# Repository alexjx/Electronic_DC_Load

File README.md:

# Electronic Controlled DC Dummy Load

An Arduino-compatible electronic load built around an ATmega328P. It draws a
controlled current from a DC source and displays the measured current, voltage,
power, temperature, and accumulated capacity.

> [!WARNING]
> This is an experimental high-power project, not a certified test instrument.
> The 15 A and 200 W values are firmware ceilings, not proven continuous hardware
> ratings. Safe operation depends on the input voltage, IRFP250N safe operating
> area, heatsink, airflow, shunt and PCB heating, wiring, connectors, calibration,
> and an external fuse. Begin with a current-limited supply at low power and do not
> leave the load unattended. The refactored firmware has not yet been validated on
> the physical hardware.

## Hardware overview

The load uses a power MOSFET as a variable resistance. A precision shunt measures
the resulting current, while the firmware adjusts a DAC until measured current
matches the requested value.

```text
Source under test -> J1 -> IRFP250N -> 5 mOhm shunt -> ground
                         ^                   |
                         |                   +-> INA213 -> AD7190 ADC
ATmega328P -> AD5541 DAC -> AD8629 gate-control amplifier
```

| Part | Purpose |
| --- | --- |
| ATmega328P-AU, 16 MHz | Runs the user interface, safety checks, and current controller |
| AD7190 | Measures load voltage and shunt current |
| AD5541 | Produces the analog current command |
| AD8629 | Buffers voltage sensing and drives the MOSFET control loop |
| INA213 and 5 mOhm / 4 W shunt | Measures load current |
| IRFP250N | Dissipates the power drawn from the source |
| LM35 | Measures heatsink temperature |
| 16x2 LCD and PCF8574 | Displays settings and measurements over I2C |
| REF5050 | Provides the 5 V ADC, DAC, and analog reference |

### Connections

| Connector | Function | Notes |
| --- | --- | --- |
| J1 | DC source under test | Schematic pad 2 is load positive; pad 1 is return/ground. Confirm this against the assembled PCB before applying power. |
| J2 | Control-power input | Feeds the MP1584 supply stage. The repository does not document a safe input-voltage range or jack polarity; verify the assembled board before use. |
| J3 | AVR ISP | Programming connector for the ATmega328P |
| J4 | Cooling fan | Nominal 12 V fan output controlled by the firmware |

The complete Eagle design is in [`schematic/`](schematic/). The design files
label the input-divider resistor as 9.9 kOhm, while the purchase record says the
fitted part is 9.09 kOhm. The firmware follows the purchase record; confirm the
assembled value and verify readings against calibrated meters before power testing.

## Controls and display

The top LCD row shows the current setpoint, cutoff voltage, and operating status.
A blank status means idle; `*` means the load is running. The LCD cursor identifies
the digit changed by the rotary encoder.

| Control | Action |
| --- | --- |
| Rotate encoder | Change the selected current or cutoff-voltage digit |
| S1 / D4 | Move the selected digit left |
| S4 / D6 | Move the selected digit right |
| S3 / D3 | Show the previous measurement page |
| S2 / D5 | Show the next measurement page |
| Hold encoder switch | Start loading after the controller has been idle for at least 3 seconds |
| Click encoder while running | Stop loading immediately |
| Click encoder on a cleared fault | Acknowledge the fault and return to idle |

The four bottom-row pages show:

1. Measured current and voltage.
2. Calculated power and heatsink temperature.
3. Session capacity in mAh.
4. Session energy in Wh.

The mAh and Wh counters reset whenever a new load session starts. The setpoints are
saved when a session starts or stops.

## Usage guide

1. With all power disconnected, inspect the board, fit an adequate heatsink and
   fan, and add a suitable external fuse to the source-under-test connection.
2. Confirm J1 polarity and the required J2 voltage and polarity from the actual
   assembled board. Connect the fan to J4, then apply control power to J2.
3. Check that the display starts normally and that no fault is reported. Verify the
   voltage, current, and temperature readings before enabling the power stage.
4. Use S1/S4 to select a digit and rotate the encoder to set the desired current and
   low-voltage cutoff. Start with a small current.
5. Turn the current-limited source off, connect it to J1 with the verified polarity,
   and then turn the source on.
6. After the controller has been idle for at least 3 seconds, hold the encoder switch
   until loading starts. Confirm that `*` appears and watch current, power, and
   temperature while testing.
7. Click the encoder to stop. Confirm that `*` disappears before disconnecting the
   source.

The firmware limits the setpoint to 15.000 A, reduces the current request above a
calculated 200 W, trips overcurrent at 16.5 A, and trips overtemperature at 95 degC.
These protections supplement rather than replace correctly rated hardware and an
external fuse.

### Faults

Any firmware fault commands the DAC to zero and latches the load off.

| Display | Meaning | Before acknowledging |
| --- | --- | --- |
| `FAULT ADC` | ADC did not initialize or respond in time | Check ADC power, SPI wiring, and ready signal |
| `FAULT TEMP SNS` | Temperature reading is outside the plausible sensor range | Check the LM35 and its wiring |
| `FAULT OVERCUR` | Measured current exceeded 16.5 A | Remove the cause of excess current |
| `FAULT UNDERVOLT` | Source voltage fell below the configured cutoff | Recharge, replace, or disconnect the source |
| `FAULT OVERTEMP` | Temperature exceeded 95 degC | Keep cooling active and wait for the load to cool |

After correcting the cause, click the encoder when the display says
`Click to ack`. Acknowledgement only returns the controller to idle; it does not
restart the load. A condition that is still unsafe will fault again or refuse to
clear.

## Firmware build and tests

Initialize the pinned libraries, then build the Arduino Uno firmware:

```sh
git submodule update --init --recursive
make -C code clean
make -C code
```

Run the hardware-independent safety and driver tests with:

```sh
make -C code/tests clean
make -C code/tests
```

See [`code/BUILDING.md`](code/BUILDING.md) for the tested Ubuntu/WSL environment,
tool versions, generated files, and current flashing limitations.

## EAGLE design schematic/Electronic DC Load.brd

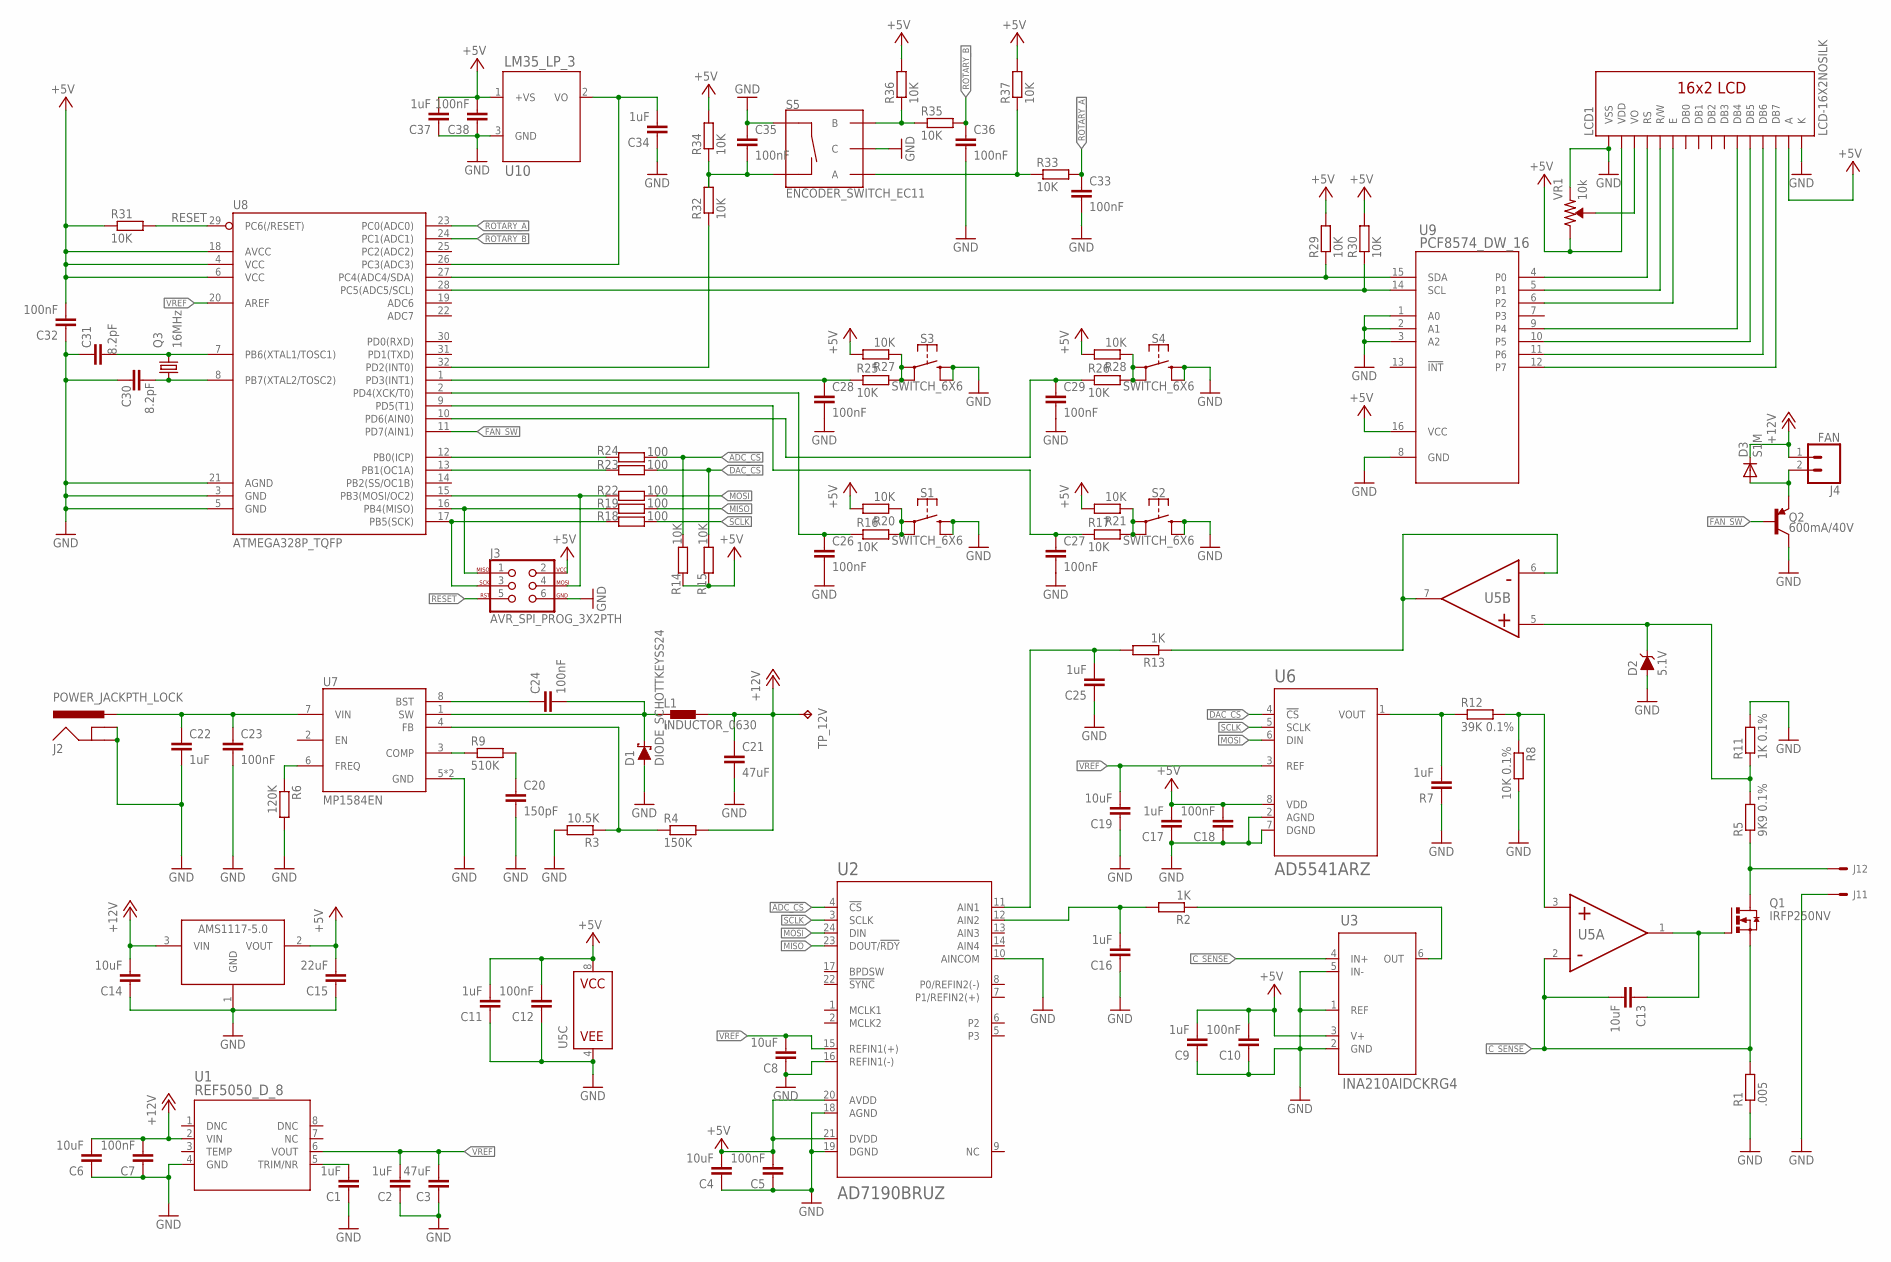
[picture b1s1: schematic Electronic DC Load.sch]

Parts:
C1, C2, C9, C11, C16, C17, C22, C25, C34, C37: 1uF; C0805
C3, C21: 47uF; C1206
C4, C6, C8, C13, C14, C19: 10uF; C1206
C5, C7, C10, C12, C18, C23, C24, C38: 100nF; C0805
C15: 22uF; C1206
C20: 150pF; C0402
C26, C27, C28, C29, C32, C33, C35, C36: 100nF; C0603
C30, C31: 8.2pF; C0603
D1: DIODE_SCHOTTKEYSS24; SMA-DIODE
D2: 5.1V; LL-34
D3: S1M; SMA
J1: KF762-2
J2: POWER_JACKPTH_LOCK; POWER_JACK_PTH_LOCK
J3: AVR_SPI_PROG_3X2PTH; 2X3
J4: FAN; 1X02_LOCK_LONGPADS
L1: INDUCTOR_0630
LCD1: LCD-16X2NOSILK; LCD-16X2_NOSILK
Q1: IRFP250NV; TO247BV
Q2: 600mA/40V; SOT23-3
Q3: 16MHz; 3.2X2.5_KX-7
R1: .005; 2728
R2, R13: 1K; R0805
R3: 10.5K; R0603
R4: 150K; R0603
R5: 9K9 0.1%; M0805
R6: 120K; R0603
R7: 1uF; C0805
R8: 10K 0.1%; R0805
R9: 510K; R0603
R11: 1K 0.1%; M0805
R12: 39K 0.1%; R0805
R14, R15: 10K; M0805
R16, R17, R20, R21, R25, R26, R27, R28, R29, R30, R31, R32, R33, R34, R35, R36, R37: 10K; R0603
R18, R19, R22, R23, R24: 100; M0805
S1, S2, S3, S4: SWITCH_6X6; SWITCH_SMD_6MM
S5: ENCODER_SWITCH_EC11; ROTARY_ENCODER_EC11
TP_12V: TPB1,27; B1,27
U1: REF5050_D_8; D8
U2: AD7190BRUZ; RU_24
U3: INA210AIDCKRG4; DCK0006A_N
U4: AMS1117-5.0; SOT223
U5: AD8629ARZ; R_8
U6: AD5541ARZ; R_8
U7: MP1584EN; SOIC9P127_490X600X170L84X42T330X241N
U8: ATMEGA328P_TQFP; TQFP32-08
U9: PCF8574_DW_16; DW16
U10: LM35_LP_3; Z03A
VR1: 10k; TRIMPOT-SMD-TC33X

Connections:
!ADC_CS: R14.2, R24.2, U2.4 (!CS)
!DAC_CS: R15.2, R23.2, U6.4 (!CS)
+5V: C4.2, C5.2, C9.2, C10.2, C11.2, C12.2, C15.2, C17.2, C18.2, C32.2, C37.2, C38.2, J3.2, LCD1.2 (VDD), LCD1.15 (A), R14.1, R15.1, R20.2, R21.2, R27.2, R28.2, R29.2, R30.2, R31.1, R34.2, R36.2, R37.2, U2.20 (AVDD), U2.21 (DVDD), U3.3 (V+), U4.2 (VOUT), U5.8 (VCC), U6.8 (VDD), U8.4 (VCC), U8.6 (VCC), U8.18 (AVCC), U9.16 (VCC), U10.1 (+VS), VR1.1 (CW)
+12V: C6.2, C7.2, C14.2, C21.1, D3.C, J4.1, L1.P$2 (2), R4.2, TP_12V.TP, U1.2 (VIN), U4.3 (VIN)
C_SENSE: C13.2, Q1.S, R1.2, U3.4 (IN+), U5.2 (IN-)
FAN_SW: Q2.1 (B), U8.11 (PD7(AIN1))
GND: C1.1, C2.1, C3.1, C4.1, C5.1, C6.1, C7.1, C8.1, C9.1, C10.1, C11.1, C12.1, C14.1, C15.1, C16.1, C17.1, C18.1, C19.1, C20.2, C21.2, C22.2, C23.2, C25.1, C26.2, C27.2, C28.2, C29.2, C30.1, C31.1, C32.1, C33.2, C34.1, C35.1, C36.2, C37.1, C38.1, D1.A, D2.A, J1.1, J2.GND, J2.GNDBREAK, J3.6, LCD1.1 (VSS), LCD1.16 (K), Q2.3 (C), R1.1, R3.2, R6.2, R7.1, R8.2, R11.2, S1.B1 (3), S1.B2 (4), S2.B1 (3), S2.B2 (4), S3.B1 (3), S3.B2 (4), S4.B1 (3), S4.B2 (4), S5.C, S5.D (SW+), U1.4 (GND), U2.10 (AINCOM), U2.16 (REFIN1(-)), U2.18 (AGND), U2.19 (DGND), U3.1 (REF), U3.2 (GND), U3.5 (IN-), U4.1 (GND), U5.4 (VEE), U6.2 (AGND), U6.7 (DGND), U7.5 (GND), U7.9 (GND), U8.3 (GND), U8.5 (GND), U8.21 (AGND), U9.1 (A0), U9.2 (A1), U9.3 (A2), U9.8 (GND), U10.3 (GND), VR1.3 (CCW)
MISO: R19.2, U2.23 (DOUT/!RDY)
MOSI: R22.2, U2.24 (DIN), U6.6 (DIN)
unnamed: R29.1, U8.27 (PC4(ADC4/SDA)), U9.15 (SDA)
unnamed: R30.1, U8.28 (PC5(ADC5/SCL)), U9.14 (SCL)
unnamed: LCD1.11 (DB4), U9.9 (P4)
unnamed: LCD1.12 (DB5), U9.10 (P5)
unnamed: LCD1.13 (DB6), U9.11 (P6)
unnamed: LCD1.14 (DB7), U9.12 (P7)
unnamed: LCD1.4 (RS), U9.4 (P0)
unnamed: LCD1.5 (R/W), U9.5 (P1)
unnamed: LCD1.6 (E), U9.6 (P2)
unnamed: C1.2, U1.5 (TRIM/NR)
unnamed: C31.2, Q3.3 (2), U8.7 (PB6(XTAL1/TOSC1))
unnamed: C30.2, Q3.1, U8.8 (PB7(XTAL2/TOSC2))
unnamed: LCD1.3 (VO), VR1.2 (WIPER)
unnamed: J1.2, Q1.D, R5.1
unnamed: C34.2, U8.26 (PC3(ADC3)), U10.2 (VO)
unnamed: C25.2, R13.2, U2.11 (AIN1)
unnamed: R6.1, U7.6 (FREQ)
unnamed: R2.1, U3.6 (OUT)
unnamed: C24.1, U7.8 (BST)
unnamed: C22.1, C23.1, J2.PWR, U7.7 (VIN)
unnamed: C24.2, D1.C, L1.P$1 (1), U7.1 (SW)
unnamed: R3.1, R4.1, U7.4 (FB)
unnamed: R9.1, U7.3 (COMP)
unnamed: C16.2, R2.2, U2.12 (AIN2)
unnamed: C20.1, R9.2
unnamed: R7.2, R12.1, U6.1 (VOUT)
unnamed: R13.1, U5.6 (IN-), U5.7 (OUT)
unnamed: D3.A, J4.2, Q2.2 (E)
unnamed: R35.1, R36.1, S5.B
unnamed: J3.3, R18.1, U8.17 (PB5(SCK))
unnamed: J3.1, R19.1, U8.16 (PB4(MISO))
unnamed: J3.4, R22.1, U8.15 (PB3(MOSI/OC2))
unnamed: R23.1, U8.13 (PB1(OC1A))
unnamed: R24.1, U8.12 (PB0(ICP))
unnamed: C13.1, Q1.G, U5.1 (OUT)
unnamed: D2.C, R5.2, R11.1, U5.5 (IN+)
unnamed: R33.1, R37.1, S5.A
unnamed: R8.1, R12.2, U5.3 (IN+)
unnamed: R16.2, R20.1, S1.A1 (1), S1.A2 (2)
unnamed: R25.2, R27.1, S3.A1 (1), S3.A2 (2)
unnamed: C35.2, R32.2, R34.1, S5.E (SW-)
unnamed: C26.1, R16.1, U8.2 (PD4(XCK/T0))
unnamed: R32.1, U8.32 (PD2(INT0))
unnamed: C28.1, R25.1, U8.1 (PD3(INT1))
unnamed: R26.2, R28.1, S4.A1 (1), S4.A2 (2)
unnamed: R17.2, R21.1, S2.A1 (1), S2.A2 (2)
unnamed: C27.1, R17.1, U8.9 (PD5(T1))
unnamed: C29.1, R26.1, U8.10 (PD6(AIN0))
RESET: J3.5, R31.2, U8.29 (PC6(/RESET))
ROTARY_A: C33.1, R33.2, U8.23 (PC0(ADC0))
ROTARY_B: C36.1, R35.2, U8.24 (PC1(ADC1))
SCLK: R18.2, U2.3 (SCLK), U6.5 (SCLK)
VREF: C2.2, C3.2, C8.2, C19.2, U1.6 (VOUT), U2.15 (REFIN1(+)), U6.3 (REF), U8.20 (AREF)

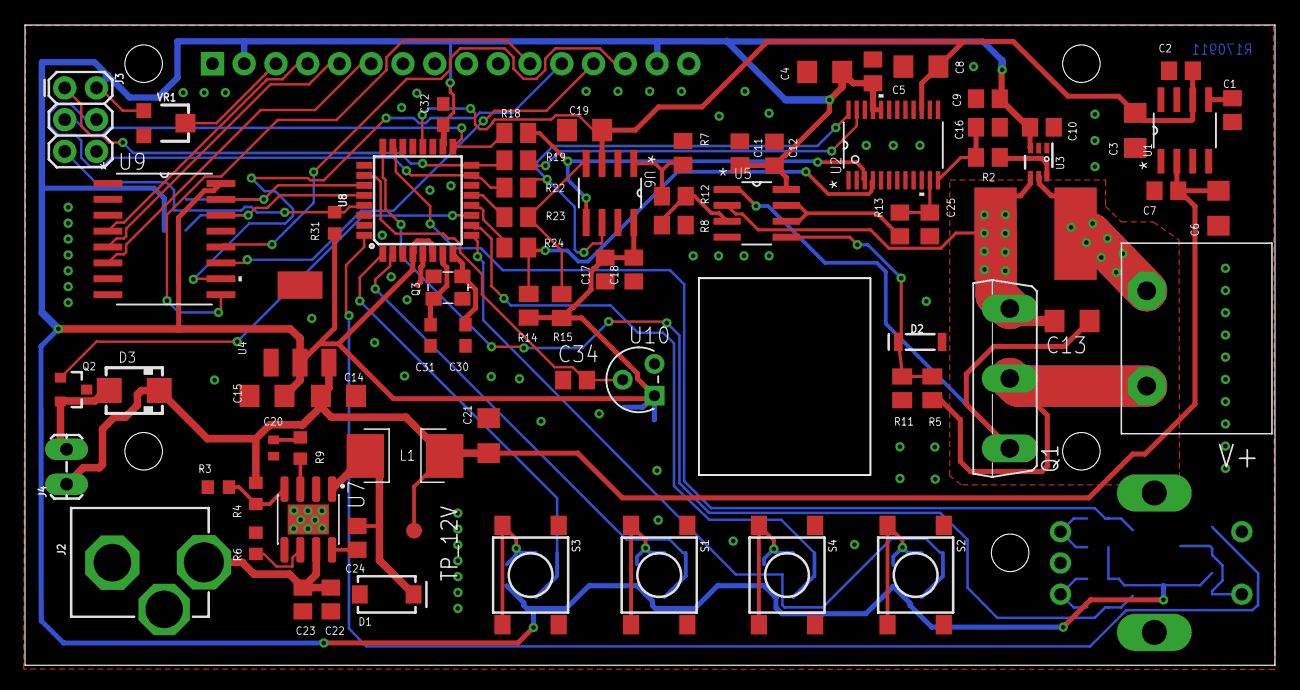
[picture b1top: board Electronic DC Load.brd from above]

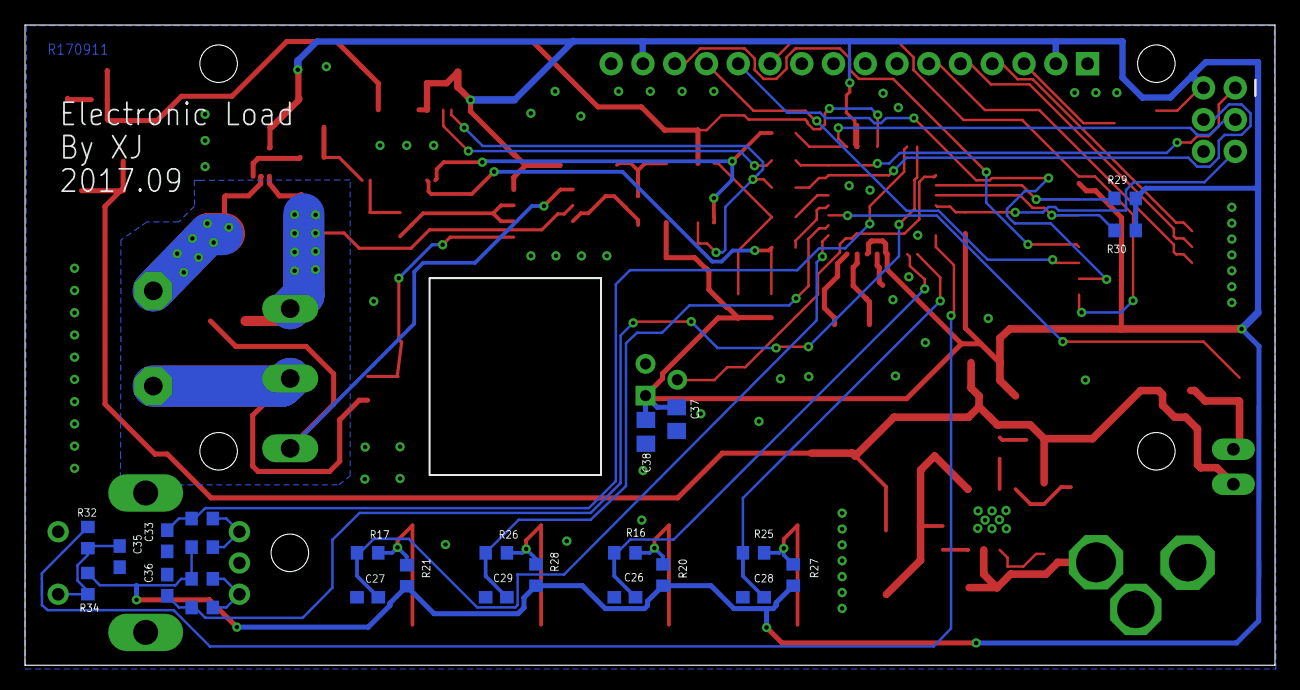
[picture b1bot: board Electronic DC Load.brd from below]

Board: 2 copper layers, 100.0 x 51.2 mm, 103 parts (25 on the bottom side), 62 nets.

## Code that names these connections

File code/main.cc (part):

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#define ENCODER_UPDATE_RATE  4


#define ADC_CS_PIN           8
#define DAC_CS_PIN           9

#define BUTTON_1_PIN         3
#define BUTTON_2_PIN         4
#define BUTTON_3_PIN         6
#define BUTTON_4_PIN         5

#define FAN_SW_PIN           7
#define LM35_PIN             A3

#define MAX_BUTTON           4
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///////////////////////

// DAC
AD5541 ad5541(DAC_CS_PIN);


// ADC
ADConverter adc(ADC_CS_PIN,
                ADC_VOLTAGE_CHN,
                ADC_CURRENT_CHN,
                VREF_VOLTAGE);
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

// FAN
FanController fan(FAN_SW_PIN);


// temperature sensor
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
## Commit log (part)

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2017-09-06 Remove the old version of schematics
2017-09-06 Update components
2017-09-06 Remove the resistor from the input pin of AD8293
2017-09-07 Add EC11 Rotary Encoder
2017-09-09 First layouts
2017-09-09 Fixed capacitors packages
2017-09-09 Remove accidentally add cycle.
2017-09-09 Make the ground connection of Rsense a litte stronger
2017-09-09 Finalized V1 for Manufacturing
2017-09-11 Fix the thermal decouple too small for PCB house
2017-09-11 Update the LCD1602 hole size to 3mm
    Dont know why SPARKFUN made the choice to use only 2.8 MM drill hole....
2017-09-11 Change debouncing filter network resistor to 1K
2017-09-15 Fix lableling errors
    Fix a few errors in the labeling of resistors and capacitors
2017-09-17 Remove the ground bridge for Rsense
    I made the ground bridge not sure if it's needed.
    And obviously, it doesn't. And removing it will tremendously increase the accuracy of INA213!!!
2017-09-22 Initial version
2017-09-23 Refactored ADC code path
2017-09-23 Clean up code
2017-09-23 Make the update function of ADC return value too
2017-09-24 Refactor Buttons
2017-09-24 Refactored FAN control
2017-09-25 Implemented the configurator
2017-09-25 PID prototype
2017-09-25 Add wattage
2017-09-25 Refactored the buttons
2017-09-25 Refactored LM35
2017-09-25 Limited the max current to 15000mA
2017-09-26 Some refactores
2017-09-26 Calibrated
2017-09-26 Tuned a bit
2017-09-26 Add a max current limitation
2017-09-26 Tune a bit more
2017-09-26 Oh no... it was not stable for anything less than 200ma
2017-09-26 Stablized...somehow.
2017-09-26 Tune even more....
2017-09-27 Make the PID frame constant
2017-09-27 Re-implemented the PID controller
2017-09-27 Tune the real PID
2017-09-27 I could not tune it better ....
2017-09-27 I guess I just did....
2017-09-27 Remove debug code
2017-10-01 Add cut off voltage
2017-10-03 Stablize the process... need clean up
2017-10-04 Add couner for wattage hour
2017-10-30 Fixed the encoder unresposive issue
2017-10-30 Add README file
2017-10-30 Fixed readme

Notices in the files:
parts and their libraries:
SparkFun-Connectors: Licensing: Creative Commons ShareAlike 4.0 International - https://creativecommons.org/licenses/by-sa/4.0
crystal-geyer_V1_0: Copyright: Geyer-Electronic
